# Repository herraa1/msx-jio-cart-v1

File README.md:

# MSX JIO CART

This is a simple MSX cartridge that allows software-based serial communications like MSXJIO but without using joystick port 2.

It includes:
* a flash ROM writable by either software (in-system from MSX-DOS) or hardware (using an external programmer)
* an I/O register to interface with the embedded serial modules
  * address of I/O register is configurable between a set of predefined options
* one or two of these serial modules (only one active at a time):
  * a RT232RL-based USB serial module
  * a Bluetooth HC-05 module
* a switch to select the active serial module
  * optional if only one module is populated

What can I do with a msx-jio-cart?

* serve a hard or floppy disk-image from a host computer (or smartphone) to your MSX, through high-speed 115200 bauds communication (either USB or Bluetooth)
* more things to come

## Current Status

* First prototype PCB sent for manufacturing as of Dec 2nd 2025 (couldn't wait to confirm some footprints...).
* After a long wait, bare prototype PCBs arrived as of Jan 8th 2026. Now, let's find some time to assemble them and (cross fingers) hope I grabbed all needed components.
* First build1 prototype successfully assembled and tested as of Jan 11th 2026.
* Another build1 cartridge successfully assembled and tested as of Jan 30th 2026.
* Third build1 cartridge successfully assembled and tested as of Feb 9th 2026.

> [!NOTE]
> Documentation in progress

## Quick Start Guide

Build and Setup
* Assemble the msx-jio-cart
* [Flash the onboard ROM](#rom-flashing-instructions)
* [Choose an I/O address](#setting-the-cartridge-io-address)
* [Setup the Bluetooth module](#bluetooth-module-setup-instructions) (if populated)
* [Set normal operation mode](#selecting-normal-operation-modes-usb-serial-and-bluetooth)

Using USB serial mode
* Move switch _SW3_ `BLUETOOTH/SERIAL` to the `right` position to use [USB serial mode](#usb-serial-mode)
* Make sure the MSX computer is powered off
* Insert the msx-jio-cart into a free slot of the MSX computer
* Connect a USB cable from your computer to the msx-jio-cart USB port (the USB and Bluetooth modules will power up)
* On your computer, prepare the disk image to be served and start the [JIO Server](https://github.com/louthrax/MSXJIO?tab=readme-ov-file#server-details) in USB serial mode
* On the JIO Server, select the correct USB device and press the connect button
* Power on the MSX computer
* The ROM will try to boot from the disk image

Using Bluetooth mode
* Move switch _SW3_ `BLUETOOTH/SERIAL` to the `left` position to use [Bluetooth mode](#bluetooth-mode)
* Make sure the MSX computer is powered off
* Insert the msx-jio-cart into a free slot of the MSX computer
* Prepare the disk image to be served and start the [JIO Server](https://github.com/louthrax/MSXJIO?tab=readme-ov-file#server-details) in Bluetooth mode
* Power on the MSX computer
* If not already done, pair your computer or Android device to the msx-jio-cart Bluetooth module
* On the JIO Server, select the correct Bluetooth device and press the connect button
* The ROM will try to boot from the disk image

## [Firmware](https://github.com/b3rendsh/msxdos2s/tree/main/jio/client)

The msx-jio-cart uses @b3rendsh [JIO clients](https://github.com/b3rendsh/msxdos2s/tree/main/jio/client) in ROM format.

There are two different ROMs available:
* MSX-DOS1 ROM [jio_dos1.rom](https://github.com/b3rendsh/msxdos2s/blob/main/jio/client/jio_dos1.rom)
  * enhanced MSX-DOS 1
  * best suited for MSX1 machines with 64K of memory
* MSX-DOS2 ROM [jio_dos2.rom](https://github.com/b3rendsh/msxdos2s/blob/main/jio/client/jio_dos2.rom)
  * enhanced MSX-DOS 2.2 / 2.31
  * works on MSX1 or higher but requires at least 128K or more RAM mapper

You can flash the ROM in-system using [HRA!](https://github.com/hra1129)'s [WRTSST.COM](https://github.com/hra1129/MSX_MegaSCC_for_SST39SF040/tree/main/tools/wrtsst) from your MSX. Or you can flash the ROM using a hardware programmer like TL866II Plus and a tool like [minipro](https://gitlab.com/DavidGriffith/minipro/).

See [ROM Flashing Instructions](#rom-flashing-instructions).

## [Software](https://github.com/louthrax/MSXJIO)

The msx-jio-cart requires one of @louthrax [JIO Servers](https://github.com/louthrax/MSXJIO/releases) to serve disk images to an MSX computer.

The JIO Server runs on a Windows, Linux or Mac computer, or alternatively on an Android device.

On the JIO server, you can select which disk image to serve and which connection method (USB serial or Bluetooth) to use. The connection method must match your current msx-jio-cart serial module selection, according to switch _SW3_ `BLUETOOTH/SERIAL`.

## [Hardware](hardware/kicad/)

The msx-jio-cart is made of a 2-layer PCB with several SMD and through-hole components placed on the front layer only:

* a 6-pin serial RT232RL USB module with DTR, TX, RX, VCC, CTS and GND signals.
* a 6-pin serial HC-05 Bluetooth module with STATE, RXD, TXD, GND, VCC and EN signals.
* a SST39SF010 1Mbit (128Kbyte) flash ROM to store the JIO client ROM
* a switch to disable the ROM at boot time (required to re-program the flash ROM from the MSX itself)
* 74HCT32 and 74HCT138 ICs to implement the I/O address selection logic and control interface
* a DIP switch to configure the I/O address of the msx-jio-cart register
* 74HCT173 and 74HCT245 to implement the I/O register
* extra TX/RX leds to signal data transmission events
* a switch to select the active serial module
* several jumpers to control the cartridge behavior and features
* a header to configure the Bluetooth module externally if required
* a cartridge-wide fuse to protect the MSX slot 5V power rail in case of a cartridge malfunction
* a Schottky diode to prevent back-powering the MSX from the serial USB module
* other active and passive components, some of them optional

### [msx-jio-cart-v1-build1](hardware/kicad/msx-jio-cart-v1-build1/)

:white_check_mark: This board has been successfully built and tested.

[Bill Of Materials (BoM)](https://htmlpreview.github.io/?https://raw.githubusercontent.com/herraa1/msx-jio-cart-v1/main/hardware/kicad/msx-jio-cart-v1-build1/bom/ibom.html)

[Schematic and PCB](https://kicanvas.org/?github=https%3A%2F%2Fgithub.com%2Fherraa1%2Fmsx-jio-cart-v1%2Ftree%2Fmain%2Fhardware%2Fkicad%2Fmsx-jio-cart-v1-build1)

|||
|-|-|
|msx-jio-cart-v1 build1<br>PCB unpopulated front|msx-jio-cart-v1 build1<br>PCB unpopulated back|

||
|:--|
|msx-jio-cart-v1 build1 PCB populated front|

#### LED indicators

| **LED**   | **State**      | **Indication** |
|-----------|----------------|----------------|
| _RX_      | On             | data is being received from the MSX |
| _TX_      | On             | data is being sent to the MSX       |

#### Switches and Jumpers

| **Switch/Jumper** | **Label**          | **State**          | **Purpose**    |
|-------------------|--------------------|--------------------|----------------|
| _SW1_             | `ROMDIS`           | **Enable**\*       | Enable Flash ROM for normal operation                                           |
| _SW1_             | `ROMDIS`           | Disable            | Disable Flash ROM (only for in-system programming)                              |
| _SW2_             | `IOSEL`            | 1,2,3 Off          | Disable I/O register (JIO CART unavailable)                                     |
| _SW2_             | `IOSEL`            | **1 On 2,3 Off**\* | Configure I/O register at 00h..07h                                              |
| _SW2_             | `IOSEL`            | 2 On 1,3 Off       | Configure I/O register at 20h..27h                                              |
| _SW2_             | `IOSEL`            | 3 On 1,2 Off       | Configure I/O register at 30h..37h                                              |
| _SW3_             | `BLUETOOTH/SERIAL` | **Left**\*         | Enable Bluetooth, leave EN floating (data mode) when JP4 1-2                    |
| _SW3_             | `BLUETOOTH/SERIAL` | Middle             | Enable Bluetooth, control EN from I/O register when JP4 1-2                     |
| _SW3_             | `BLUETOOTH/SERIAL` | **Right**\*        | Enable USB                                                                      |
| _JP4_             | `BTENCTL`          | **1-2**\*          | Control EN according to SW3 position                                            |
| _JP4_             | `BTENCTL`          | 2-3                | Set EN high unconditionally (AT mode)                                           |

\* Default settings

#### Advanced jumpers

| **Jumper** | **Label**        | **State**          | **Purpose**    |
|------------|------------------|--------------------|----------------|
| _JP3_      | -                | **Open**\*         | (Advanced) Populate R4 and R5, drive Bluetooth EN signal using 3V3 logic        |
| _JP3_      | -                | Closed             | (Advanced) Do NOT populate R4 and R5, drive Bluetooth EN signal using 5V logic  |
| _JP2_      | -                | **Open**\*         | (Advanced) Populate R2 and R3, drive Bluetooth RXD signal using 3V3 logic       |
| _JP2_      | -                | Closed             | (Advanced) Do NOT populate R2 nor R3, drive Bluetooth RXD signal using 5V logic |
| _JP1_      | -                | **1-2**\*          | (Advanced) Populate C5 and U5, MSX reset causes reset/zeroing of I/O reg        |
| _JP1_      | -                | 2-3                | (Advanced) Do NOT populate C5 nor U5, I/O reg is never reset/zeroed             |

\* Default settings

#### Headers

| **Header** | **Label**        | **Purpose**    |
|------------|------------------|----------------|
| _J1_       | `EXTPROG`        | Allows to configure the Bluetooth module via AT commands externally |

## Cartridge Initial Setup

Setting up the msx-jio-cart for the first time involves the following tasks:
* flashing the onboard ROM
* choosing an I/O address
* and setting up the Bluetooth module (if populated)

### ROM Flashing Instructions

#### Flashing the ROM from MSX-DOS

1. Prepare your bootable MSX-DOS media (a floppy disk, a mass storage device, etc.)
2. Copy [WRTSST.COM](https://github.com/hra1129/MSX_MegaSCC_for_SST39SF040/blob/main/tools/wrtsst/WRTSST.COM) to your MSX-DOS media
3. Copy the JIO client ROMs [jio_dos1.rom](https://github.com/b3rendsh/msxdos2s/blob/main/jio/client/jio_dos1.rom) for DOS 1.x and [jio_dos2.rom](https://github.com/b3rendsh/msxdos2s/blob/main/jio/client/jio_dos2.rom) for DOS 2.x to your MSX-DOS media
4. Move the _SW1_ `ROMDIS` switch to the _disabled_ position (see [Switches and jumpers](#switches-and-jumpers))
5. With your MSX powered off, insert your bootable MSX-DOS media and insert the msx-jio-cart into an empty slot
6. Power on and boot your MSX with your MSX-DOS media
7. Once on the MSX-DOS prompt, move the _SW1_ `ROMDIS` switch to the _enabled_ position (see [Switches and jumpers](#switches-and-jumpers))

> [!WARNING]
> Make sure you select the right slot before using `WRTSST.COM`.
> If you select the wrong slot, or do not select a slot, and you happen to have other `SST39SF*` compatible Flash ROMs in your MSX system, you may end up erasing and overwriting the wrong IC.

8. To flash the `jio_dos1.rom` into the _msx-jio-cart_ inserted in _slot 1_, execute the following command in the MSX-DOS prompt:

   ~~~Shell
   WRTSST /S1 JIO_DOS1.ROM
   ~~~

   Change the /Sx parameter to the actual slot number where the msx-jio-cart is inserted.

8. To flash the `jio_dos2.rom` into the _msx-jio-cart_ inserted in _slot 1_, execute the following command in the MSX-DOS prompt:

   ~~~Shell
   WRTSST /S1 JIO_DOS2.ROM
   ~~~

   Change the /Sx parameter to the actual slot number where the msx-jio-cart is inserted.

#### Flashing the ROM using a TL866II Plus and minipro from Linux

1. Install [minipro](https://gitlab.com/DavidGriffith/minipro/) into your Linux box
2. Insert the `SST39SF010` PLLC32 Flash ROM IC into a PLCC32 to DIP32 adapter, taking into account the orientation markings
3. Insert the PLCC32 to DIP32 adapter into the `TL866II Plus`, again taking into account the orientation markings
4. Connect your `TL866II Plus` to a USB port of your Linux box
5. Check that the Flash ROM IC is correctly identified.
   It should indicate a Chip ID of `0xBFB5`.

   ~~~bash
   ./minipro -p SST39SF010@PLCC32 -D
   ~~~
   ~~~
   Found TL866II+ 04.2.132 (0x284)
   Device code: 02114104
   Serial code: DVJZVC8IFBXAEQ55JFIU
   USB speed: 12Mbps (USB 1.1)
   Chip ID: 0xBFB5  OK
   ~~~

6. Build a 128K file named `128kdos1.bin` with the `jio_dos1.rom` contents at the correct offset executing the following command:

   ~~~bash
   cat <(dd if=/dev/zero ibs=16k count=1 | LC_ALL=C tr "\000" "\377") jio_dos1.rom <(dd if=/dev/zero ibs=96k count=1 | LC_ALL=C tr "\000" "\377") > 128kdos1.bin
   ~~~

7. Build a 128K file named `128kdos2.bin` with the `jio_dos2.rom` contents at the correct offset executing the following command:

   ~~~bash
   cat <(dd if=/dev/zero ibs=16k count=1 | LC_ALL=C tr "\000" "\377") jio_dos2.rom <(dd if=/dev/zero ibs=80k count=1 | LC_ALL=C tr "\000" "\377") > 128kdos2.bin
   ~~~

8. To flash the `128kdos1.bin` for DOS 1.x into the Flash ROM, execute the following command:

   ~~~bash
   ./minipro -p SST39SF010@PLCC32 -w 128kdos1.bin
   ~~~
   ~~~
   Found TL866II+ 04.2.132 (0x284)
   Device code: 02114104
   Serial code: DVJZVC8IFBXAEQ55JFIU
   USB speed: 12Mbps (USB 1.1)
   Chip ID: 0xBFB5  OK
   Erasing... 0.40Sec OK
   Writing Code...  6.40Sec  OK
   Reading Code...  0.98Sec  OK
   Verification OK
   ~~~

9. To flash the `128kdos2.bin` for DOS 2.x into the Flash ROM, execute the following command:

   ~~~bash
   ./minipro -p SST39SF010@PLCC32 -w 128kdos2.bin
   ~~~
   ~~~
   Found TL866II+ 04.2.132 (0x284)
   Device code: 02114104
   Serial code: DVJZVC8IFBXAEQ55JFIU
   USB speed: 12Mbps (USB 1.1)
   Chip ID: 0xBFB5  OK
   Erasing... 0.40Sec OK
   Writing Code...  6.40Sec  OK
   Reading Code...  0.98Sec  OK
   Verification OK
   ~~~

### I/O Address Selection

See [Setting the cartridge I/O address](#setting-the-cartridge-io-address).

### Bluetooth Module Setup Instructions

Using the JIO Server with Bluetooth requires preparing the msx-jio-cart Bluetooth module for 115200 bauds operation.
Also, assigning a unique name to the Bluetooth module is recommended to easily locate the right msx-jio-cart.

This setup is only needed when setting up the Bluetooth module for the first time.

#### Selecting Bluetooth AT configuration mode at 38400 bauds

In this mode, the Bluetooth module can be configured via AT commands using a fixed 38400 baud rate, irrespective of the currently configured baud rate at the module.

To enable Bluetooth AT configuration mode at 38400 bauds, remove the msx-jio-cart from the MSX computer and move the _SW1_ `ROMDIS` handle to the `right` (disable) position, move the _SW3_ `BLUETOOTH/SERIAL` handle to the `left` (Bluetooth) position and set the _JP4_ `BTENCTL` jumper to the `2-3` position.

| **Switch/Jumper** | **Label**          | **State**          | **Purpose**    |
|-------------------|--------------------|--------------------|----------------|
| _SW1_             | `ROMDIS`           | Disable            | Disable Flash ROM (only for in-system programming or HC-05 re-configuration)    |
| _SW3_             | `BLUETOOTH/SERIAL` | **Left**\*         | Enable Bluetooth, leave EN floating (data mode) when JP4 1-2                    |
| _JP4_             | `BTENCTL`          | 2-3                | Set EN high unconditionally (AT mode)                                           |

##### Identifying AT mode 38400 baud state

A msx-jio-cart inserted into a MSX cartridge slot, powered on and configured in Bluetooth AT configuration mode at 38400 bauds, shows the following Bluetooth module LED pattern continuously:
* the LED goes on for 2 seconds approximately
* and then goes off for 1 second

#### Using the JIOC38K MSX tool to configure the Bluetooth module

The JIOC38K tool can be run from a MSX computer to send AT commands at 38400 bauds to the msx-jio-cart Bluetooth module when operating in 38400 baud rate AT mode. The tool can be launched from BASIC either from tape or disk.

##### Loading JIOC38K from tape

1. Make sure your MSX computer is powered off
2. Insert the msx-jio-cart cartridge [configured for AT 38400 mode](#selecting-bluetooth-at-configuration-mode-at-38400-bauds) into a free cartridge slot of your MSX computer
3. Connect the tape interface of your MSX computer to a computer or mobile device with an audio jack output connector and able to play WAV files
4. Power on your MSX and proceed to the BASIC prompt
5. Type the following instruction to load JIOC38K from tape and press `Enter`
   ~~~bash
   RUN"CAS:
   ~~~
6. From the computer or mobile device, play the [JIOC38K.wav](software/JIOC38K.wav) file
7. On the MSX computer, a tape record named J38K will be found, and the JIOC38K tool will load and run

##### Loading JIOC38K from disk (or other media)

Using an auxiliar computer:
1. Prepare your MSX-DOS media (a floppy disk, a mass storage device, etc.)
2. Copy [JIOC38K.BAS](software/JIOC38K.BAS) and [JIOC38K.BIN](software/JIOC38K.BIN) to your MSX-DOS media

Using your MSX computer:
1. Make sure your MSX computer is powered off
2. Insert the msx-jio-cart cartridge [configured for AT 38400 mode](#selecting-bluetooth-at-configuration-mode-at-38400-bauds) into a free cartridge slot of your MSX computer
3. Power on your MSX computer and make sure you are at the BASIC prompt
4. With the MSX-DOS media inserted. type the following instruction to load JIOC38K from media and press `Enter`

   ~~~bash
   RUN"JIOC38K.BAS
   ~~~

##### Using JIOC38K

These are general guidelines when using JIOC38K:
* The JIOC38K tool will report on startup the currently configured I/O address of the msx-jio-cart if detected.

* If no msx-jio-cart is detected, the JIOC38K tool will error out and exit to BASIC.

* AT commands can be entered freely as in BASIC mode: an AT command will only be sent once `Enter` is pressed over the line with the command.
* If you receive an `ERROR` response, check the AT command for proper syntax and try again.
* The very first AT command executed may fail.
* Pressing and releasing the `CTRL` key forces cancellation of reply reception mode in case that the Bluetooth module does not provide a reply to a command.
* Pressing `CTRL-C` exits JIOC38K and returns to the BASIC prompt.

On your MSX computer:
* Type `AT` and press `Enter` to check if you can communicate with the Bluetooth module using AT commands.
  The Bluetooth module will reply with an `OK` prompt if everything works right. If you receive an error or a garbled reply, repeat the command until you get an `OK`reply.
* Type `AT+NAME=yourname` and press `Enter` to name the Bluetooth module with `yourname`.
* Type `AT+UART=115200,0,0` and press `Enter` to configure the Bluetooth module for 115200 baud operation.
* Type `AT+NAME?` and press `Enter` to check the configured name.
* Type `AT+UART?` and press `Enter` to check the configured baudrate.

The new configuration is automatically saved to the Bluetooth module.

Once finished, power off your MSX computer and re-configure the msx-jio-cart for [Bluetooth normal operation](#bluetooth-mode).

## Cartridge Operation

### Setting the cartridge I/O address

With the cartridge removed from the MSX and without power applied, slide only one of the three switches in the _SW2_ `IOSEL` DIP switch to the `ON` position to select one of the possible I/O address ranges.

See the [Switches and jumpers](#switches-and-jumpers) section to determine which I/O address range is enabled by each switch.

> [!WARNING]
> Make sure that the I/O address selected does not overlap any other I/O address used by other cartridges connected to the MSX computer.
>
> If unsure, check your other MSX cartridges documentation and/or [Grauw list of I/O ports](https://map.grauw.nl/resources/msx_io_ports.php).

> [!NOTE]
> Depending on which orientation was used when the DIP switch was soldered, the numbering and the `ON` position side may be different. Always use the numbering of the cartridge silkscreen to identify the `1`, `2` and `3` switches (not the numbering of the DIP switch) and always use the DIP switch `ON` position marking to determine the ON position.

> [!TIP]
> The JIO function of the MSX JIO cartridge can be disabled by setting all of the `1`, `2` and `3` switches to the `OFF` position. 

### Selecting normal operation modes (USB serial and Bluetooth)

In normal operation modes, make sure the _SW1_ `ROMDIS` handle is in the `left` (enable) position and the _JP4_ `BTENCTL` jumper is in the `1-2` position.

| **Switch/Jumper** | **Label**          | **State**          | **Purpose**    |
|-------------------|--------------------|--------------------|----------------|
| _SW1_             | `ROMDIS`           | **Enable**\*       | Enable Flash ROM for normal operation                                           |
| _JP4_             | `BTENCTL`          | **1-2**\*          | Control EN according to SW3 position                                            |

#### USB serial mode

To enable USB serial mode move the _SW3_ `BLUETOOTH/SERIAL` handle to the `right` (USB serial) position, and make sure _SW1_ is already setup for [normal operation mode](#selecting-normal-operation-modes-usb-serial-and-bluetooth).

| **Switch/Jumper** | **Label**          | **State**          | **Purpose**    |
|-------------------|--------------------|--------------------|----------------|
| _SW3_             | `BLUETOOTH/SERIAL` | **Right**\*        | Enable USB                                                                      |

##### Identifying USB serial mode

In USB serial mode, the USB module RX and TX LEDs blink at the same time as the cartridge RX and TX LEDs.

#### Bluetooth mode

To enable Bluetooth mode move the _SW3_ `BLUETOOTH/SERIAL` handle to the `left` or `middle` (Bluetooth) position, and make sure _SW1_ and _JP4_ are already setup for [normal operation mode](#selecting-normal-operation-modes-usb-serial-and-bluetooth).

This mode should only be used once the Bluetooth module has been configured at 115200 bauds.

| **Switch/Jumper** | **Label**          | **State**          | **Purpose**    |
|-------------------|--------------------|--------------------|----------------|
| _SW3_             | `BLUETOOTH/SERIAL` | **Left**\*/Middle  | Enable Bluetooth                                                                |

##### Identifying non-paired/unconnected state Bluetooth mode

In this mode, the Bluetooth module is waiting for another unpaired device to pair, or from a previously paired device to connect. The LED blinks 5 times per second approximately.

##### Identifying connected state Bluetooth mode

In this mode, the Bluetooth module is connected to a paired device. The LED blinks twice in a second, then goes off for two seconds, repeating this pattern continuously.

## Cartridge Programming Interface

The msx-jio-cart implements a single 8-bit I/O register in the MSX Z80 [I/O address](#setting-the-cartridge-io-address) space for Bluetooth and USB serial module data and control.

### I/O Register Format

Register format considerations:
* IN direction is from module to MSX
* OUT direction is from MSX to module
* LSB is bit 0, MSB is bit 7
* Data bits are common to USB serial and Bluetooth modes
* Control bits are specific to each module
* Output control bits have safe defaults for normal operation

#### Register format for USB serial mode

This register format is available when _SW3_ `BLUETOOTH/SERIAL` is in the `right` position.

| **bit** | **type** | **direction** | **description**                                                                                           |
| ------- | -------- | ------------- | --------------------------------------------------------------------------------------------------------- |
| 0       | data     | IN            | data received from USB serial to MSX                                                                      |
| 1       | control  | IN            | serial data terminal ready (`DTR`)                                                                        |
| 2       | data     | IN/OUT        | transmit data from MSX to USB serial when written, last data transmitted from MSX to USB serial when read |
| 3       | control  | IN/OUT        | serial clear to send (`CTS`) when written, last `CTS` value written when read                             |
| 4       | control  | IN            | always 0                                                                                                  |
| 5       | control  | IN            | always 0                                                                                                  |
| 6       | data     | IN            | last data transmitted from MSX to USB serial                                                              |
| 7       | control  | IN            | last `CTS` value written                                                                                  |

#### Register format for Bluetooth mode

This register format is available when _SW3_ `BLUETOOTH/SERIAL` is in the `middle` or `left` positions.

| **bit** | **type** | **direction** | **description**                                                                                                                 |
| ------- | -------- | ------------- | ------------------------------------------------------------------------------------------------------------------------------- |
| 0       | data     | IN            | data received from Bluetooth to MSX                                                                                             |
| 1       | control  | IN            | `state` of Bluetooth connection, as reported by Bluetooth module (varies depending on actual HC-05 Bluetooth module)            |
| 2       | data     | IN/OUT        | transmit data from MSX to Bluetooth when written, last data transmitted from MSX to Bluetooth when read                         |
| 3      | control  | IN/OUT        | `EN` (enable) value when written, last `EN` value written when read.<br>When _JP4_ `BTENCTL` is set to 1-2 and _SW3_ `BLUETOOTH/SERIAL` is in the `middle` position, you can set `EN` to 1 to enter [_partial AT_ mode](https://www.martyncurrey.com/arduino-with-hc-05-bluetooth-module-at-mode), 0 for normal data mode  |
| 4       | control  | IN            | always 0                                                                                                                        |
| 5       | control  | IN            | always 0                                                                                                                        |
| 6       | data     | IN            | last data transmitted from MSX to Bluetooth                                                                                     |
| 7       | control  | IN            | last `EN` value written                                                                                                         |

### Transmit data to module

* Write a `0` to `bit 2` to assert the transmit line
* Write a `1` to `bit 2` to deassert the transmit line

### Receive data from module

* Read `bit 0`: a `0` means an asserted line, a `1` a deasserted line

## Compatibility Tests

| **Model**                                                                           | **msx-jio-cart v1 build1** |
|-------------------------------------------------------------------------------------|----------------------------|
| [Sony MSX HB-101P](https://www.msx.org/wiki/Sony_HB-101P)                           |           OK               |
| [Sony MSX HB-501F](https://www.msx.org/wiki/Sony_HB-501F)                           |           OK               |
| [Toshiba MSX HX-10P](https://www.msx.org/wiki/Toshiba_HX-10P)                       |           OK               |
| [Philips MSX2 VG-8235](https://www.msx.org/wiki/Philips_VG-8235)                    |           OK               |
| [Panasonic MSX2+ FS-A1WSX](https://www.msx.org/wiki/Panasonic_FS-A1WSX) (non-turbo) |           OK               |
| [Omega MSX2+](https://github.com/skiselev/omega)                                    |           OK               |
| [Tides Rider](https://genami.shop/products/tides-rider-hdk) (non-turbo)             |           OK               |
| [JFF-TMSHAT](https://github.com/herraa1/JFF-TMSHAT)                                 |           OK               |
| [uMSX](https://theretrohacker.com/2022/07/08/yet-another-fpga-based-msx-the-umsx/)  |           OK               |
| [Philips NMS8255](https://www.msx.org/wiki/Philips_NMS_8255)                        |           OK               |
| [Philips VG8010](https://www.msx.org/wiki/Philips_VG-8010) with 512KB RAM extension |           OK               |
| [Casio PV-7](https://www.msx.org/wiki/Casio_PV-7)                                   |           OK               |
| [National CF-3000](https://www.msx.org/wiki/National_CF-3000)                       |           OK               |
| [Panasonic FS-A1ST](https://www.msx.org/wiki/Panasonic_FS-A1ST) (non-turbo)         |           OK               |

## Errata / Known Issues

* On some MSX systems, by design or due to the aging of some components, the voltage supplied to the cartridge slots is suboptimal and the Bluetooth module of a msx-jio-cart with both USB serial and Bluetooth modules installed may be slower or even randomly disconnect. The cause is likely the additional voltage drop within the cartridge due to the reverse current protection diode that protects the MSX from being back-powered from the USB serial module.

  A workaround for this problem affecting only the Bluetooth module is to connect the msx-jio-cart USB port to a 5V USB power supply or data port of a computer, as the USB connector of the USB serial module can back-power the Bluetooth module (but never the MSX). By doing this, the Bluetooth module and USB serial module are powered directly by 5V from the USB connection.

* The silkscreen of Build1 incorrectly shows SST39SF040 for U1. It should show SST39SF010 instead.

* The current JIO client ROMs are designed for the standard MSX Z80 clock frequency of ~3.579545 MHz, so they won't work when enabling so called "turbo" modes (which change the CPU frequency) on capable MSX machines.

* The [MSX-PICO](https://msxpico.com/) cartridge by default adds wait cycles that may break the strict timing required by the Z80 code used to serialize data at 115200 bauds.

## msx-jio-cart early prototype

## Acrylic Enclosure

This acrylic enclosure is designed for the msx-jio-cart with bluetooth and usb serial modules and a large mechanical switch for selecting the serial interface.

The enclosure is based on the nice [acrylic enclosures by Capsule5000](https://github.com/capsule5000/CARTRIDGE_METHACRYLATE_MSX-EEPROM-Cartridge-64k).

### [Enclosure](enclosure/)

|||
|-|-|
|front|back|

## References

NYYRIKKI's 115200 bps routines
* https://www.msx.org/forum/msx-talk/development/software-rs-232-115200bps-on-msx

b3rendsh msxdos2s
* https://github.com/b3rendsh/msxdos2s

Louthrax MSXJIO
* https://github.com/louthrax/MSXJIO

Skoti's Spider Flash Cart
* https://github.com/konkotgit/MSX-Spider-Flash-Cart

Danjovic Soda-IDE
* https://github.com/Danjovic/Soda-IDE

Capsule5000 acrylic enclosures
* https://github.com/capsule5000?tab=repositories

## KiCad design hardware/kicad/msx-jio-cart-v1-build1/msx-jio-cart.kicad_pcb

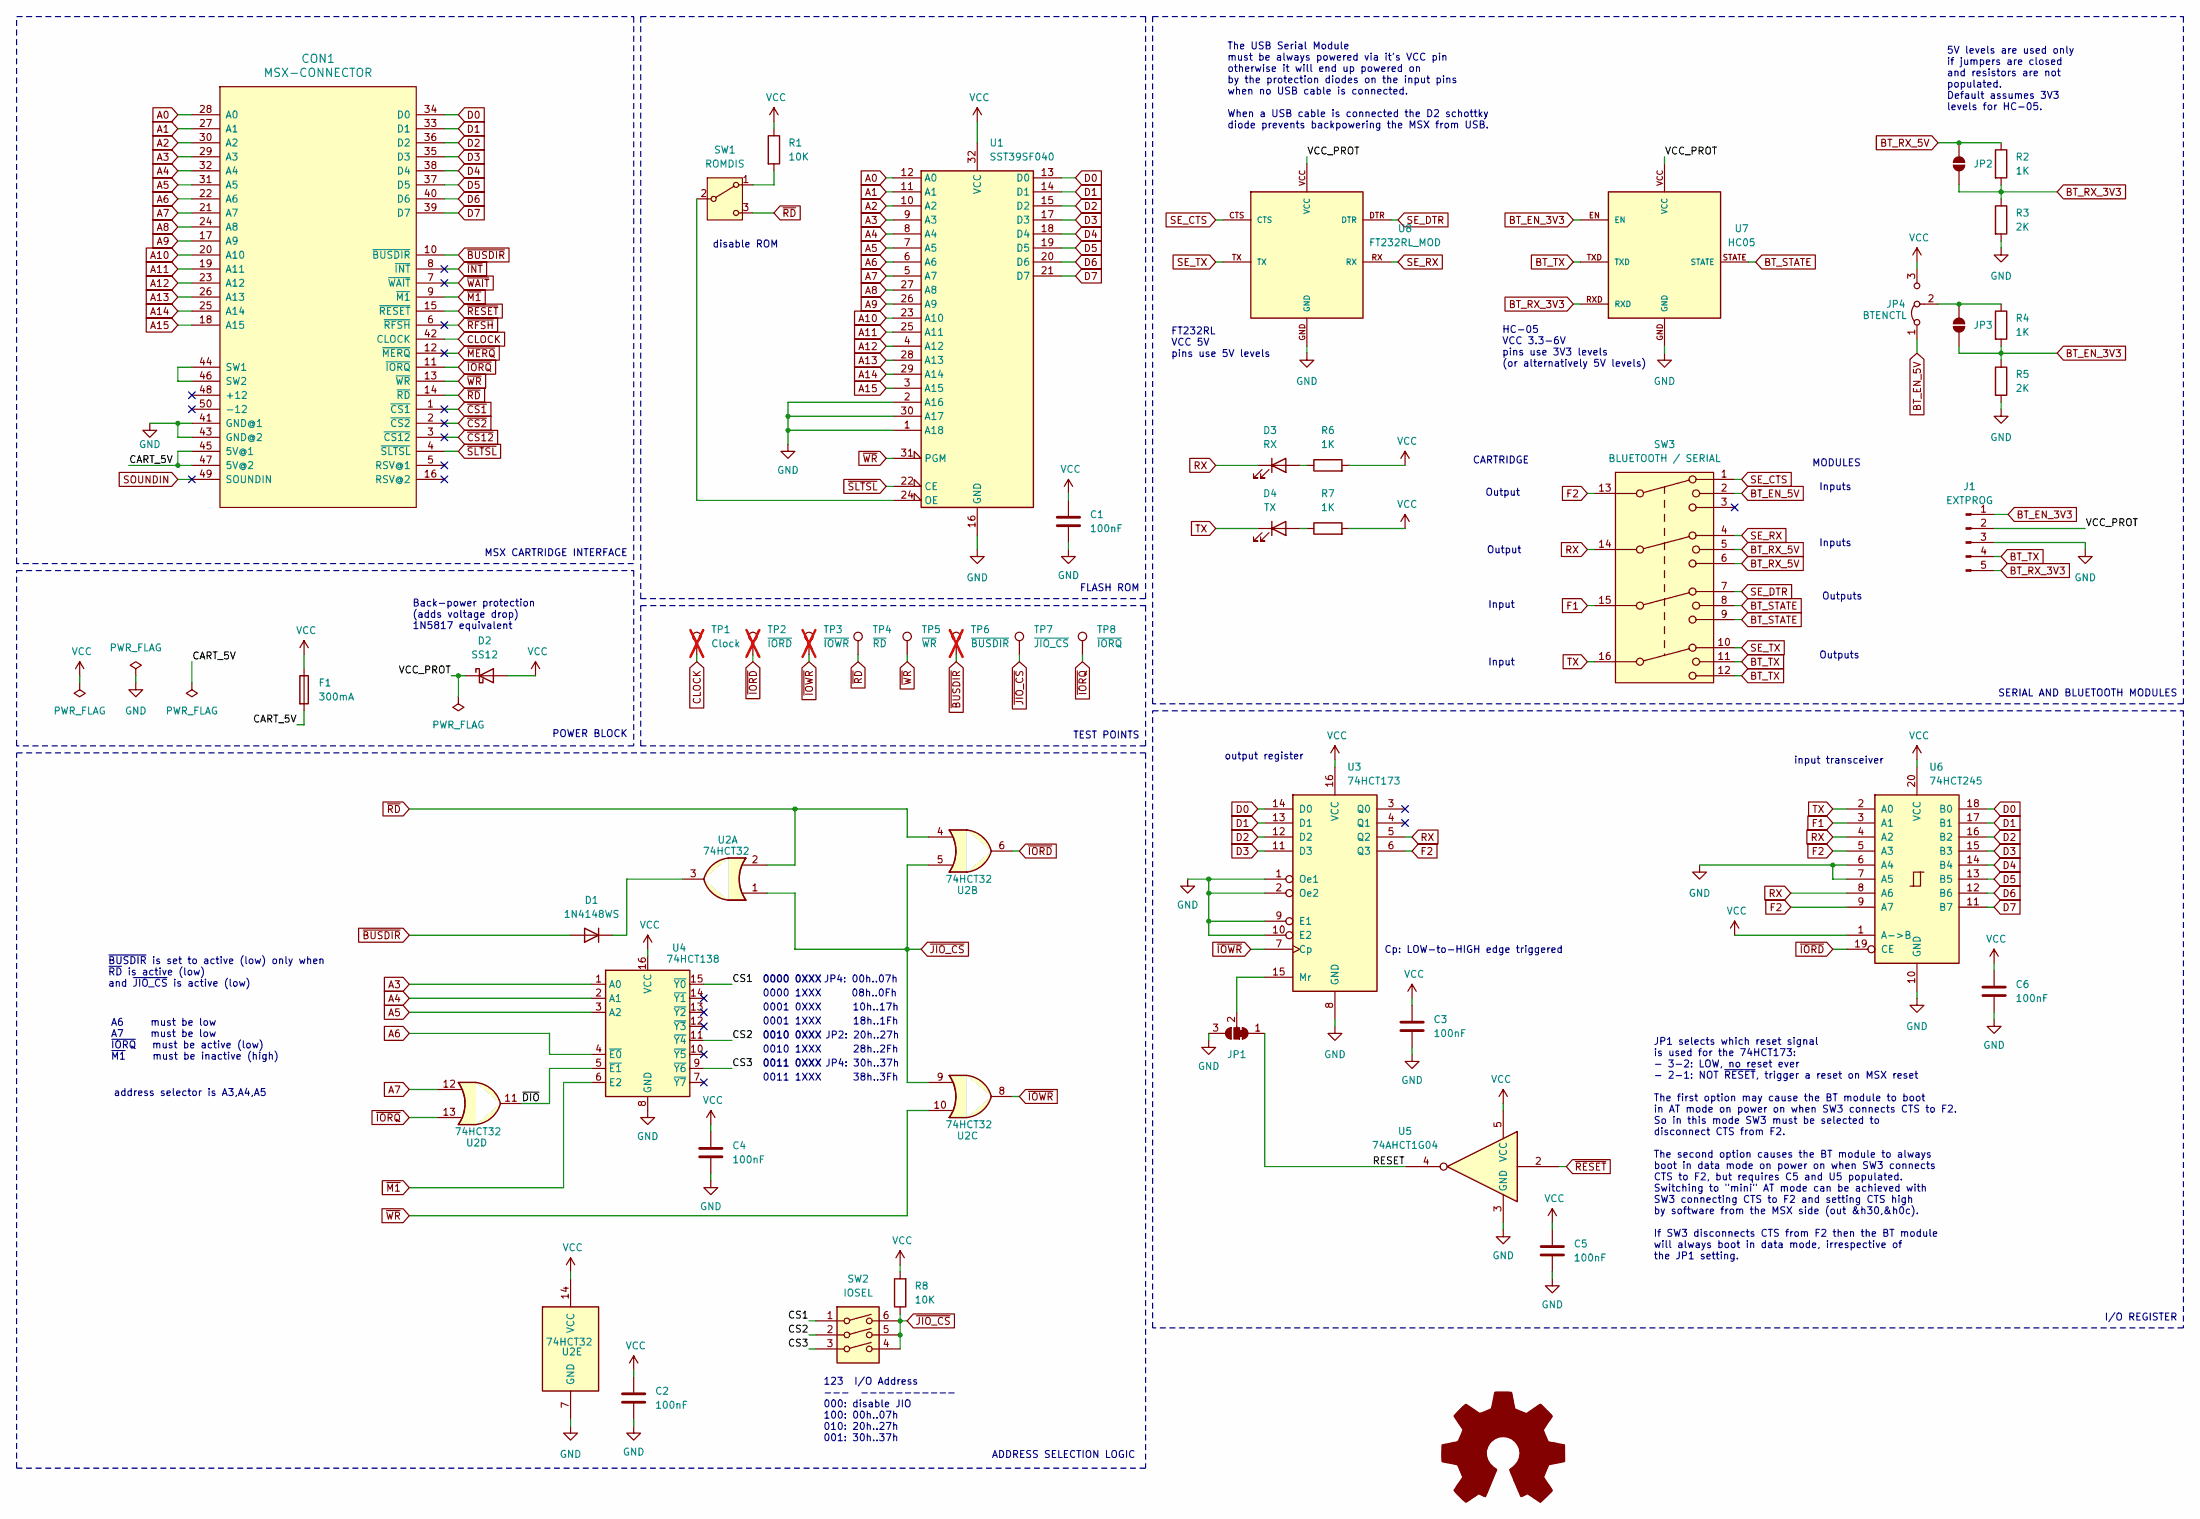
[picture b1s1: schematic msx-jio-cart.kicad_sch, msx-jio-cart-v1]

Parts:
C1, C2, C3, C4, C5, C6: 100nF; C_0805_2012Metric_Pad1.18x1.45mm_HandSolder
CON1: MSX-CONNECTOR; CARTRIDGE_MSX_NOCUT
D1: 1N4148WS; D_SOD-323_HandSoldering
D2: SS12; D_SMA_Handsoldering
D3: RX; LED_0805_2012Metric_Pad1.15x1.40mm_HandSolder
D4: TX; LED_0805_2012Metric_Pad1.15x1.40mm_HandSolder
F1: 300mA; Fuse_1206_3216Metric_Pad1.42x1.75mm_HandSolder
J1: EXTPROG; PinHeader_1x05_P2.54mm_Horizontal
JP1: SolderJumper_3_Bridged12; SolderJumper-3_P1.3mm_Bridged12_RoundedPad1.0x1.5mm
JP2: JP2; SolderJumper-2_P1.3mm_Open_TrianglePad1.0x1.5mm
JP3: JP3; SolderJumper-2_P1.3mm_Open_TrianglePad1.0x1.5mm
JP4: BTENCTL; PinHeader_1x03_P2.54mm_Horizontal
R1, R8: 10K; R_0805_2012Metric_Pad1.20x1.40mm_HandSolder
R2, R4, R6, R7: 1K; R_0805_2012Metric_Pad1.20x1.40mm_HandSolder
R3, R5: 2K; R_0805_2012Metric_Pad1.20x1.40mm_HandSolder
SW1: ROMDIS; SW_SK-12D07G6-1P2T-6mm
SW2: IOSEL; SW_DIP_SPSTx03_Slide_6.7x9.18mm_W7.62mm_P2.54mm_LowProfile
SW3: BLUETOOTH / SERIAL; SW_SK-43D01-4P3T-Xmm
SYM1: Logo_Open_Hardware_Large; OSHW-Logo_7.5x8mm_SilkScreen
TP1: Clock; TestPoint_THTPad_D1.5mm_Drill0.7mm; not fitted
TP2: ~{IORD}; TestPoint_Pad_D1.5mm; not fitted
TP3: ~{IOWR}; TestPoint_Pad_D1.5mm; not fitted
TP4: ~{RD}; TestPoint_Pad_D1.5mm
TP5: ~{WR}; TestPoint_Pad_D1.5mm
TP6: ~{BUSDIR}; TestPoint_Pad_D1.5mm; not fitted
TP7: ~{JIO_CS}; TestPoint_Pad_D1.5mm
TP8: ~{IORQ}; TestPoint_Pad_D1.5mm
U1: SST39SF040; PLCC-32_11.4x14.0mm_P1.27mm-socket
U2: 74HCT32; SOIC-14_3.9x8.7mm_P1.27mm
U3: 74HCT173; SOIC-16_3.9x9.9mm_P1.27mm
U4: 74HCT138; SOIC-16_3.9x9.9mm_P1.27mm
U5: 74AHCT1G04; SOT-23-5_HandSoldering
U6: 74HCT245; SOIC-20W_7.5x12.8mm_P1.27mm
U7: HC05
U8: FT232RL_MOD; FT232RL-MOD

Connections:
/CART_5V: CON1.45 (5V@1), CON1.47 (5V@2), F1.2
/CS1: SW2.1, U4.15 (~Y0)
/CS2: SW2.2, U4.11 (~Y4)
/CS3: SW2.3, U4.9 (~Y6)
/RESET: JP1.1 (A), U5.4
/VCC_PROT: D2.1 (K), J1.2, U7.VCC, U8.VCC
/~DIO: U2.11, U4.5 (~E1)
A0: CON1.28 (A0), U1.12 (A0)
A1: CON1.27 (A1), U1.11 (A1)
A2: CON1.30 (A2), U1.10 (A2)
A3: CON1.29 (A3), U1.9 (A3), U4.1 (A0)
A4: CON1.32 (A4), U1.8 (A4), U4.2 (A1)
A5: CON1.31 (A5), U1.7 (A5), U4.3 (A2)
A6: CON1.22 (A6), U1.6 (A6), U4.4 (~E0)
A7: CON1.21 (A7), U1.5 (A7), U2.12
A8: CON1.24 (A8), U1.27 (A8)
A9: CON1.17 (A9), U1.26 (A9)
A10: CON1.20 (A10), U1.23 (A10)
A11: CON1.19 (A11), U1.25 (A11)
A12: CON1.23 (A12), U1.4 (A12)
A13: CON1.26 (A13), U1.28 (A13)
A14: CON1.25 (A14), U1.29 (A14)
A15: CON1.18 (A15), U1.3 (A15)
BT_EN_3V3: J1.1, JP3.2 (B), R4.2, R5.1, U7.EN
BT_EN_5V: JP4.1 (A), SW3.2
BT_RX_3V3: J1.5, JP2.2 (B), R2.2, R3.1, U7.RXD
BT_RX_5V: JP2.1 (A), R2.1, SW3.5, SW3.6
BT_STATE: SW3.8, SW3.9, U7.STATE
BT_TX: J1.4, SW3.11, SW3.12, U7.TXD
CLOCK: CON1.42 (CLOCK), TP1.1
D0: CON1.34 (D0), U1.13 (D0), U3.14 (D0), U6.18 (B0)
D1: CON1.33 (D1), U1.14 (D1), U3.13 (D1), U6.17 (B1)
D2: CON1.36 (D2), U1.15 (D2), U3.12 (D2), U6.16 (B2)
D3: CON1.35 (D3), U1.17 (D3), U3.11 (D3), U6.15 (B3)
D4: CON1.38 (D4), U1.18 (D4), U6.14 (B4)
D5: CON1.37 (D5), U1.19 (D5), U6.13 (B5)
D6: CON1.40 (D6), U1.20 (D6), U6.12 (B6)
D7: CON1.39 (D7), U1.21 (D7), U6.11 (B7)
F1: SW3.15, U6.3 (A1)
F2: SW3.13, U3.6 (Q3), U6.5 (A3), U6.9 (A7)
GND: C1.2, C2.2, C3.2, C4.2, C5.2, C6.2, CON1.41 (GND@1), CON1.43 (GND@2), J1.3, JP1.3 (B), R3.2, R5.2, U1.1 (A18), U1.2 (A16), U1.16 (GND), U1.30 (A17), U2.7 (GND), U3.1 (Oe1), U3.2 (Oe2), U3.8 (GND), U3.9 (E1), U3.10 (E2), U4.8 (GND), U5.3 (GND), U6.6 (A4), U6.7 (A5), U6.10 (GND), U7.GND, U8.GND
unnamed: CON1.44 (SW1), CON1.46 (SW2)
unnamed: D1.1 (K), U2.3
unnamed: D3.2 (A), R6.1
unnamed: D4.2 (A), R7.1
unnamed: JP1.2 (C), U3.15 (Mr)
unnamed: JP3.1 (A), JP4.2 (C), R4.1
unnamed: R1.2, SW1.1 (A)
unnamed: SW1.2 (B), U1.24 (OE)
RX: D3.1 (K), SW3.14, U3.5 (Q2), U6.4 (A2), U6.8 (A6)
SE_CTS: SW3.1, U8.CTS
SE_DTR: SW3.7, U8.DTR
SE_RX: SW3.4, U8.RX
SE_TX: SW3.10, U8.TX
SOUNDIN: CON1.49 (SOUNDIN)
TX: D4.1 (K), SW3.16, U6.2 (A0)
VCC: C1.1, C2.1, C3.1, C4.1, C5.1, C6.1, D2.2 (A), F1.1, JP4.3 (B), R1.1, R6.2, R7.2, R8.2, U1.32 (VCC), U2.14 (VCC), U3.16 (VCC), U4.16 (VCC), U5.5 (VCC), U6.1 (A->B), U6.20 (VCC)
~BUSDIR: CON1.10 (~BUSDIR), D1.2 (A), TP6.1
~CS1: CON1.1 (~CS1)
~CS2: CON1.2 (~CS2)
~CS12: CON1.3 (~CS12)
~INT: CON1.8 (~INT)
~IORD: TP2.1, U2.6, U6.19 (CE)
~IORQ: CON1.11 (~IORQ), TP8.1, U2.13
~IOWR: TP3.1, U2.8, U3.7 (Cp)
~JIO_CS: R8.1, SW2.4, SW2.5, SW2.6, TP7.1, U2.1, U2.5, U2.9
~M1: CON1.9 (~M1), U4.6 (E2)
~MERQ: CON1.12 (~MERQ)
~RD: CON1.14 (~RD), SW1.3 (C), TP4.1, U2.2, U2.4
~RESET: CON1.15 (~RESET), U5.2
~RFSH: CON1.6 (~RFSH)
~SLTSL: CON1.4 (~SLTSL), U1.22 (CE)
~WAIT: CON1.7 (~WAIT)
~WR: CON1.13 (~WR), TP5.1, U1.31 (PGM), U2.10

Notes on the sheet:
output register
HC-05 VCC 3.3-6V pins use 3V3 levels (or alternatively 5V levels)
Inputs
10h..17h
0000 1XXX
CARTRIDGE
~{BUSDIR} is set to active (low) only when ~{RD} is active (low) and ~{JIO_CS} is active (low)
JP1 selects which reset signal is used for the 74HCT173: - 3-2: LOW, no reset ever - 2-1: NOT ~{RESET}, trigger a reset on MSX reset The first option may cause the BT module to boot in AT mode on power on when SW3 connects CTS to F2. So in this mode SW3 must be selected to disconnect CTS from F2. T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
FT232RL VCC 5V pins use 5V levels
JP2: 20h..27h
0000 0XXX
28h..2Fh
0001 1XXX
Outputs
Cp: LOW-to-HIGH edge triggered
MSX CARTRIDGE INTERFACE
disable ROM
A6 must be low A7 must be low ~{IORQ} must be active (low) ~{M1} must be inactive (high)
POWER BLOCK
JP4: 00h..07h
SERIAL AND BLUETOOTH MODULES
ADDRESS SELECTION LOGIC
08h..0Fh
18h..1Fh
TEST POINTS
address selector is A3,A4,A5
123 I/O Address --- ----------- 000: disable JIO 100: 00h..07h 010: 20h..27h 001: 30h..37h
0011 1XXX
5V levels are used only if jumpers are closed and resistors are not populated. Default assumes 3V3 levels for HC-05.
0011 0XXX
I/O REGISTER
FLASH ROM
Input
JP4: 30h..37h
Output
38h..3Fh
Back-power protection (adds voltage drop) 1N5817 equivalent
MODULES
input transceiver
0010 1XXX

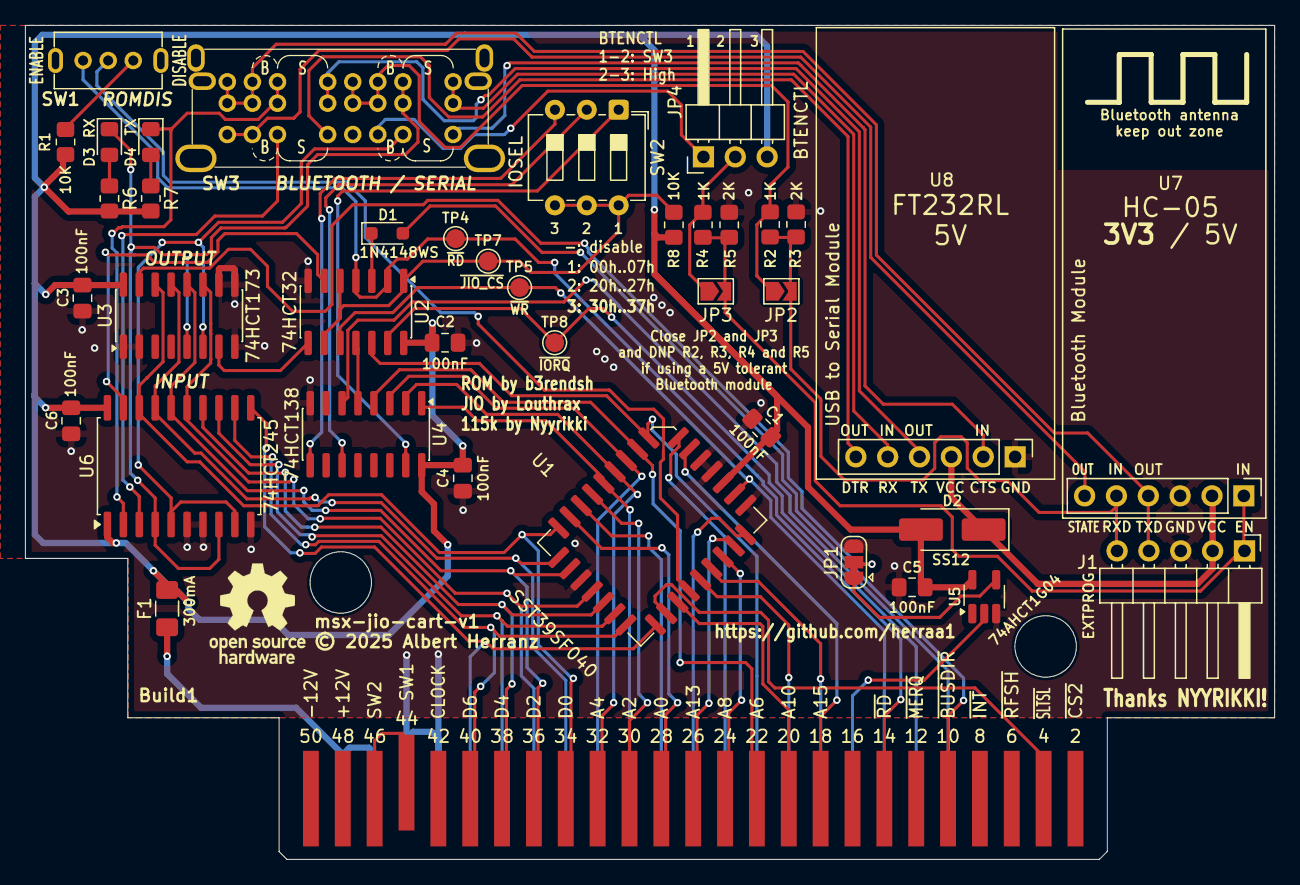
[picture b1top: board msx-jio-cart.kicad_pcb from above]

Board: 2 copper layers, 99.6 x 66.5 mm, 41 parts (0 on the bottom side), 65 nets.

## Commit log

2025-12-02 Initial commit.
2025-12-02 No flux capacitor yet.
2025-12-03 fixed bin filename in bas bloader
2025-12-05 fixed wrong link
2025-12-07 add ^Z ending to BAS file
2025-12-07 add BASIC jiocart probing example
2025-12-07 add z80 assembly jiocart probing example
2025-12-08 jioctest: leave EN low after probing
2025-12-08 jsm115k: reformat whitespace
2026-01-08 update status
2026-01-11 build1 successfully built
2026-01-15 readme: add compatibility tests and issues section
2026-01-15 tested Sony HB-101P
2026-01-17 tested uMSX
2026-01-18 kicad: fixed schematic comment
2026-01-21 documentation enhancements
2026-01-22 add initial flashing instructions
2026-02-01 readme: add initial cartridge setup and operation info
2026-02-01 s/slider/handle/
2026-02-01 fix incorrect instructions for bluetooth normal mode
2026-02-04 add jioc config tools, enhance doc
2026-02-04 readme: fix markup link
2026-02-06 clarify usb and bt enable modes, fix typo
2026-02-09 added programming interface section, enhance doc
2026-02-09 fix quotes
2026-02-10 added quick start guide
2026-02-17 minor doc updates, add new tested models
2026-02-17 errata: silkscreen for U1
2026-02-25 readme: added cart with case image
2026-02-25 add Casio PV-7 to compatibility tests
2026-02-25 minor redaction fixes
2026-02-26 add info about turbo and other timing disturbances
2026-02-27 fix htmlpreview link
2026-02-28 add acrylic enclosure
2026-02-28 add missing enclosure images
2026-02-28 make main cartridge image smaller

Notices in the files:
hardware/kicad/msx-jio-cart-v1-build1/msx-jio-cart.kicad_pcb:
© 2025 Albert Herranz
